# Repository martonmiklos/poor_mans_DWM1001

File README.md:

# Poor man's DWM1001

(Or the rich one's it depends on the perspective.)

I happened to buy a few DWM1000s from the mouser. When they arrived I have realized that the Decawave have just released the DWM1001 modules with a supported software stack, etc. So I deciced to create a board which hosts a E73-2G4M04S BLE module and provides connection to my DWM1000 breakout boards. The HW provides the same connections what the DWM1001 has just in bigger size. 

Drawn in EAGLE 8.x

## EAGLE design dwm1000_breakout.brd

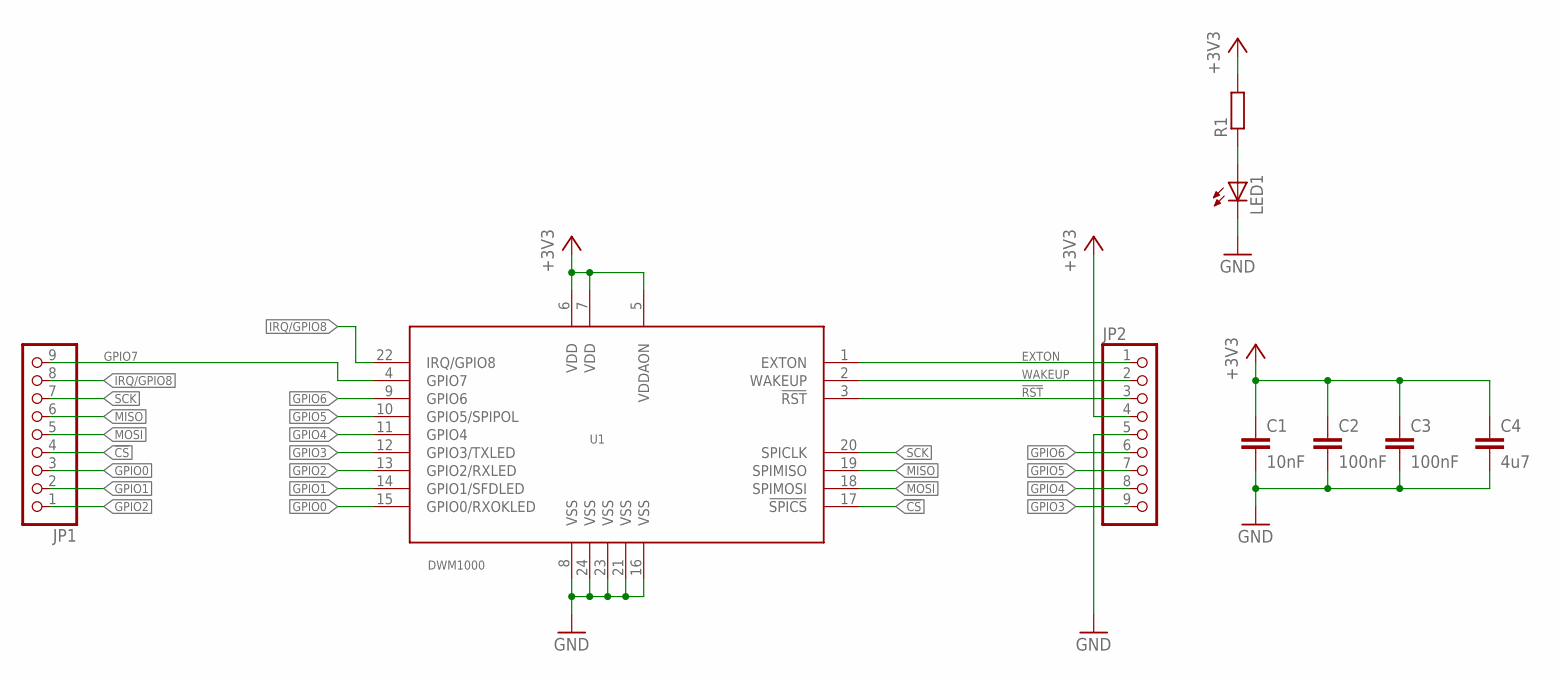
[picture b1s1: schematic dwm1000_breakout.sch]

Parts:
C1: 10nF; C0603
C2, C3: 100nF; C0603
C4: 4u7; C0805K
JP1, JP2: PINHD-1X9; 1X09
LED1: LEDCHIP-LED0603; CHIP-LED0603
R1: R-EU_R0603; R0603
U1: DWM1000

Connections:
!CS: JP1.4, U1.17 (!SPICS)
!RST: JP2.3, U1.3 (!RST)
+3V3: C1.1, C2.1, C3.1, C4.1, JP2.4, R1.2, U1.5 (VDDAON), U1.6 (VDD), U1.7 (VDD)
EXTON: JP2.1, U1.1 (EXTON)
GND: C1.2, C2.2, C3.2, C4.2, JP2.5, LED1.C, U1.8 (VSS), U1.16 (VSS), U1.21 (VSS), U1.23 (VSS), U1.24 (VSS)
GPIO0: JP1.3, U1.15 (GPIO0/RXOKLED)
GPIO1: JP1.2, U1.14 (GPIO1/SFDLED)
GPIO2: JP1.1, U1.13 (GPIO2/RXLED)
GPIO3: JP2.9, U1.12 (GPIO3/TXLED)
GPIO4: JP2.8, U1.11 (GPIO4)
GPIO5: JP2.7, U1.10 (GPIO5/SPIPOL)
GPIO6: JP2.6, U1.9 (GPIO6)
GPIO7: JP1.9, U1.4 (GPIO7)
IRQ/GPIO8: JP1.8, U1.22 (IRQ/GPIO8)
MISO: JP1.6, U1.19 (SPIMISO)
MOSI: JP1.5, U1.18 (SPIMOSI)
unnamed: LED1.A, R1.1
SCK: JP1.7, U1.20 (SPICLK)
WAKEUP: JP2.2, U1.2 (WAKEUP)

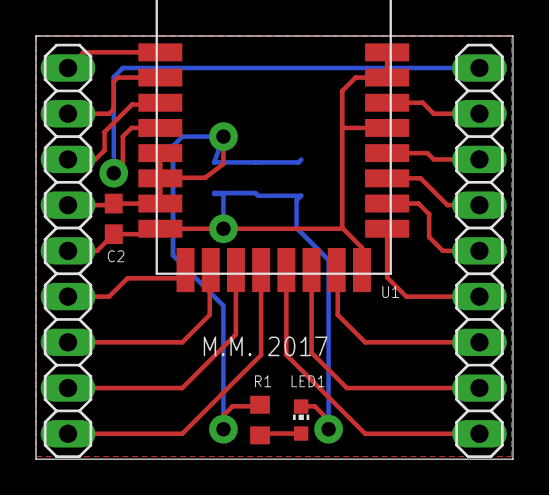
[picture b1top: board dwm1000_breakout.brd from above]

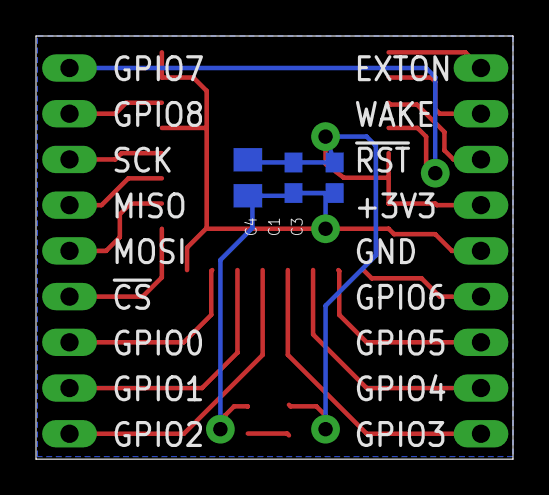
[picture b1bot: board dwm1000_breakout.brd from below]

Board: 2 copper layers, 26.5 x 23.5 mm, 9 parts (3 on the bottom side), 19 nets.

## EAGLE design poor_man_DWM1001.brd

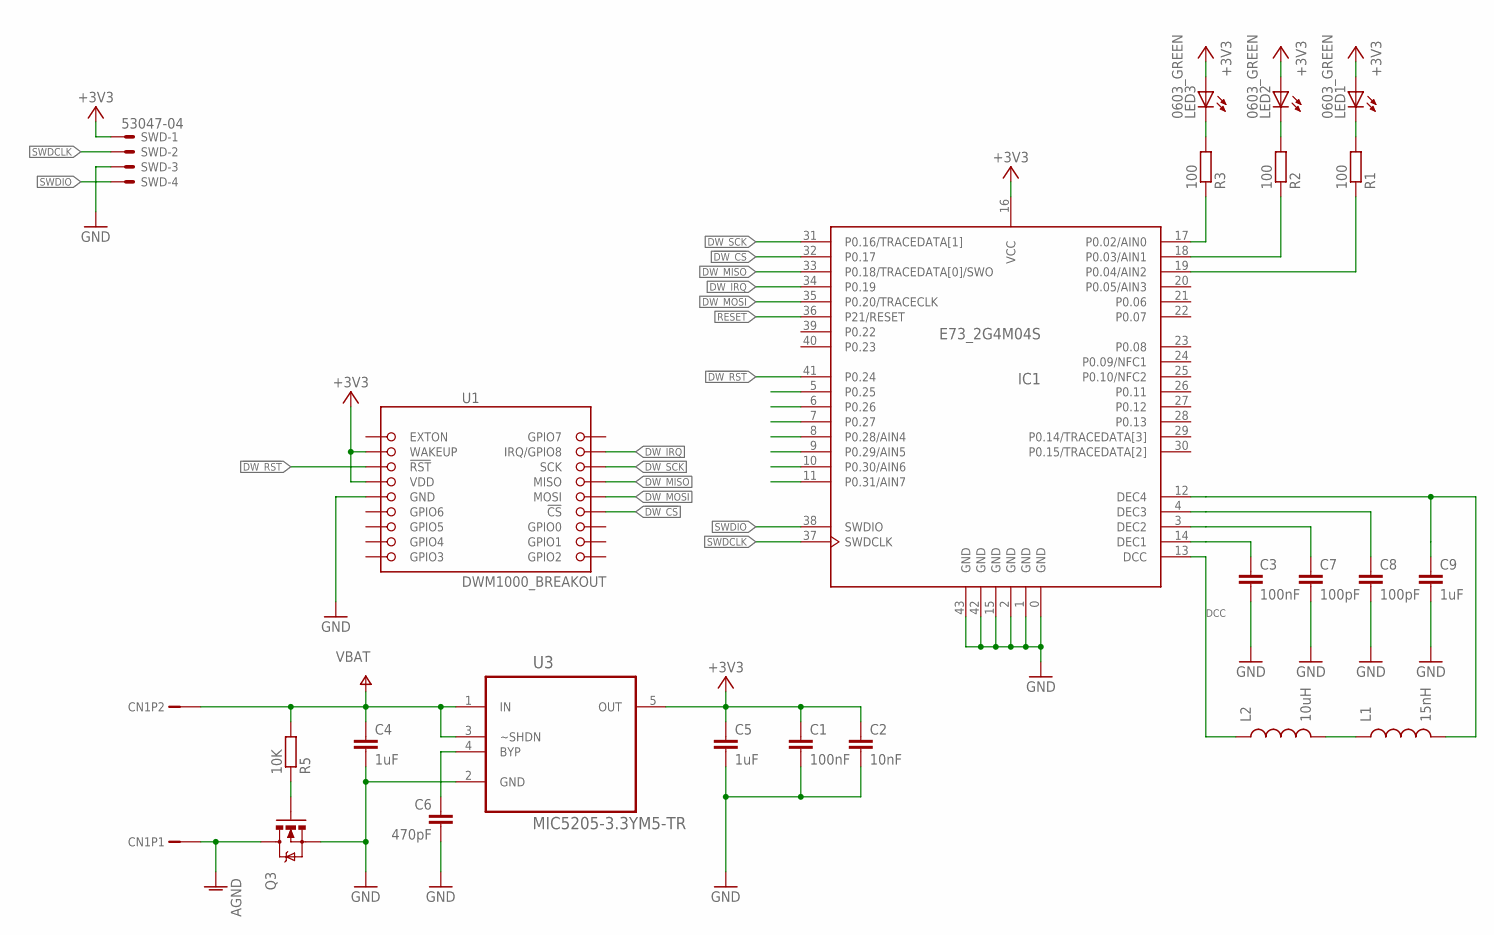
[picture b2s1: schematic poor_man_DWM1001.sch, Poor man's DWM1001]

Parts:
C1, C3: 100nF; C0603
C2: 10nF; C0603
C4, C5, C9: 1uF; C0603
C6: 470pF; C0603
C7, C8: 100pF; C0603
CN1: B2B-PH-K-S
IC1: E73_2G4M04S
L1: 15nH; SPARKFUN_C0402
L2: 10uH; SPARKFUN_0603
LED1, LED2, LED3: 0603_GREEN; CHIP-LED0603
Q3: MOSFET-NCHANNELSMD; SOT23-3
R1, R2, R3: 100; R0603
R5: 10K; R0603
SWD: 53047-04
U1: DWM1000_BREAKOUT
U3: MIC5205-3.3YM5-TR; SOT95P280X145-5N

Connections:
!DW_CS: IC1.32 (P0.17), U1.6 (!CS)
!DW_RST: IC1.41 (P0.24), U1.16 (!RST)
+3V3: C1.1, C2.1, C5.1, IC1.16 (VCC), LED1.A, LED2.A, LED3.A, SWD.1, U1.15 (VDD), U1.17 (WAKEUP), U3.5 (OUT)
AGND: CN1.1, Q3.3 (D)
ANTISTUPID_GATE: Q3.1 (G), R5.1
DCC: IC1.13 (DCC), L2.1
DEC1: C3.1, IC1.14 (DEC1)
DEC2: C7.1, IC1.3 (DEC2)
DEC3: C8.1, IC1.4 (DEC3)
DEC4: C9.1, IC1.12 (DEC4), L1.2
DW_IRQ: IC1.34 (P0.19), U1.2 (IRQ/GPIO8)
DW_MISO: IC1.33 (P0.18/TRACEDATA[0]/SWO), U1.4 (MISO)
DW_MOSI: IC1.35 (P0.20/TRACECLK), U1.5 (MOSI)
DW_SCK: IC1.31 (P0.16/TRACEDATA[1]), U1.3 (SCK)
GND: C1.2, C2.2, C3.2, C4.2, C5.2, C6.2, C7.2, C8.2, C9.2, IC1.0 (GND), IC1.1 (GND), IC1.2 (GND), IC1.15 (GND), IC1.42 (GND), IC1.43 (GND), Q3.2 (S), SWD.3, U1.14 (GND), U3.2 (GND)
GPIO_LED1: IC1.19 (P0.04/AIN2), R1.1
GPIO_LED1_R: LED1.C, R1.2
GPIO_LED2: IC1.18 (P0.03/AIN1), R2.1
GPIO_LED2_R: LED2.C, R2.2
GPIO_LED3: IC1.17 (P0.02/AIN0), R3.1
GPIO_LED3_R: LED3.C, R3.2
MIC_BYPASS: C6.1, U3.4 (BYP)
unnamed: L1.1, L2.2
RESET: IC1.36 (P21/RESET)
SWDCLK: IC1.37 (SWDCLK), SWD.2
SWDIO: IC1.38 (SWDIO), SWD.4
VBAT: C4.1, CN1.2, R5.2, U3.1 (IN), U3.3 (~SHDN)

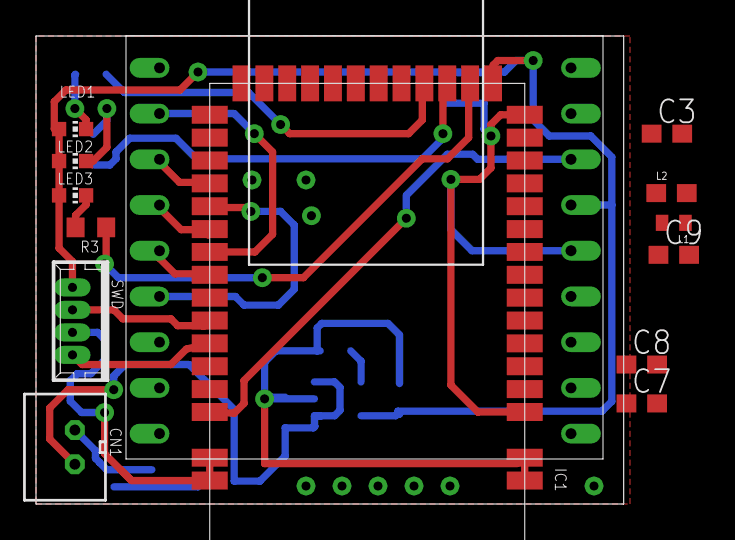
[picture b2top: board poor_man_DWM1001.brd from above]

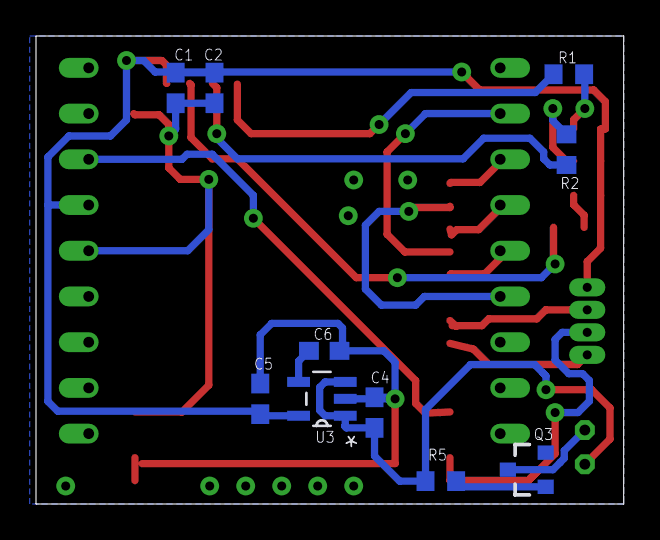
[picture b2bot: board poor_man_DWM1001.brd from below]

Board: 2 copper layers, 32.6 x 26.0 mm, 24 parts (10 on the bottom side), 26 nets.

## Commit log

2018-04-25 Initial add
2018-04-25 Readme Update
2018-04-26 Daily save
2018-04-26 Silkscreen fixes
2018-04-26 - Updated net names
2021-10-09 Added DWM1000 board

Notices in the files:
parts and their libraries:
SparkFun: Licensing: CC v3.0 Share-Alike You are welcome to use this library for commercial purposes.
